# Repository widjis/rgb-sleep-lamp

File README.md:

# RGB Sleep Lamp

A USB-C-powered RGB lamp with a 3D-printed enclosure, an ESP-12F controller, and a WS2812B LED strip. This repository preserves the mechanical design, electronics revisions, custom libraries, fabrication exports, and design-review evidence.

## Mechanical design

| Assembled lamp | Transparent internal view |
| --- | --- |
|  |  |

These saved CAD previews illustrate the enclosure and internal arrangement; the component blocks in the transparent view are placement references. The latest editable enclosure is the native FreeCAD document linked below.

[Open the FreeCAD design](mechanical/freecad/RGB%20Sleep%20Lamp.FCStd) · [Assembly animation](mechanical/freecad/RGB-Sleep-Lamp-native-assembly.mp4) · [Exploded-view animation](mechanical/freecad/RGB-Sleep-Lamp-explode-reverse.mp4)

## Open the current designs

| Design | Main file |
| --- | --- |
| Editable mechanical enclosure | [RGB Sleep Lamp.FCStd](mechanical/freecad/RGB%20Sleep%20Lamp.FCStd) |
| Electronics E5 project | [circuit.kicad_pro](electronic-design/revisions/5/circuit.kicad_pro) |
| E5 PCB | [circuit.kicad_pcb](electronic-design/revisions/5/circuit.kicad_pcb) |
| E5 schematic | [circuit.kicad_sch](electronic-design/revisions/5/circuit.kicad_sch) |
| E5 fabrication package | [Gerber ZIP](electronic-design/revisions/5/fabrication/20261031-E5/RGB-Sleep-Lamp-E5-Gerber-20261031.zip) |

Open the electronics through its KiCad project so the included project settings and local footprint library are available. The E5 layout was saved and checked with KiCad 10.0.7. Custom footprints, artwork and component models are included beside the design files.

## Hardware

- ESP-12F / ESP8266 controller.
- WS2812B strip: 50 cm, 60 LEDs/metre, 30 LEDs total.
- Power architecture: USB-C PD source, PDC004 fixed-20 V trigger module, 5 V buck converter, then 3.3 V regulation for the controller.
- The LED strip operates from the 5 V rail. No mains circuitry is inside the enclosure.
- Rounded PCB outline, three mounting holes, GPIO/programming headers and LED output connector.

## E5 status

All E4 track/via routing was removed and rebuilt. E5 retains the physical component placement, pad geometry/nets, models, PCB outline and curved ORANGEFLAVOR LABS artwork. Reference labels were adjusted around the new via holes.

- Minimum track width and copper-clearance rule: **0.3 mm**.
- All 33 vias: **0.8 mm drill / 1.2 mm outside copper diameter**.
- Approximately 71.85% of routed track length is on the top layer.
- Top power/GND pours and bottom GND pour are included.
- Recorded native DRC: **0 violations, 0 unconnected items, 0 schematic-parity issues**, with all DRC checks active and no exclusions.
- Native board renders, GerbView review and fabrication ZIP checksums are recorded in [validation.json](electronic-design/revisions/5/validation.json).

These are digital validation results from 2026-10-31. Physical fit, donor-component dimensions/values, thermal, RF and functional testing remain provisional or not run. The fabrication package is marked `PRODUCTION_REVIEW_PENDING`.

[Bottom view](electronic-design/revisions/5/renders/pcb-e5-bottom.png) · [DRC report](electronic-design/revisions/5/drc-final.rpt)

## Repository layout

- `mechanical/freecad/`: native working enclosure, checkpoints, review images and assembly media.
- `mechanical/revisions/`: preserved mechanical revisions through R9 and their original source/exports. These historical exports may differ from the newer editable FreeCAD document.
- `mechanical/printing/`: existing printer-specific print outputs.
- `electronic-design/revisions/`: preserved electronics E1–E5, libraries, models, checks and exports.
- `electronic-design/planning/`: earlier placement and mechanical-planning material.
- `documentation/`: attachments, design checks, named backups and original project metadata.

Relative compatibility links such as `current-electronics`, `current-mechanical`, `electronics`, and `revisions` are preserved. `electronic-design/current` points to E5; `mechanical/current` points to the R9 export snapshot. Use the editable FreeCAD file above for ongoing enclosure work.

Named design checkpoints and explicit revision folders are versioned. OS metadata, editor locks, KiCad local UI state and editor-internal `.history` repositories stay local.

## Firmware

Application firmware and Google Home integration are planned; this initial import contains the hardware design. WLED, a custom ESP8266 firmware, and the integration approaches discussed for the lamp have not yet been installed or validated on this hardware.

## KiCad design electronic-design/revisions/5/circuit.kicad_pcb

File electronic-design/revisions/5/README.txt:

RGB SLEEP LAMP - ELECTRONICS REVISION E5

Rebuilt from E4 after removing all 444 track segments and 34 vias. All routing objects in E5 have new UUIDs. Physical footprints, pad geometry/nets, placement, 43 component models, 47 reference labels, curved artwork and board outline are retained. Five reference labels and two board labels were adjusted to keep clear of the new via bores; a short R12 leader was added.

RULES
- Clearance >=0.3 mm; every actual track width >=0.3 mm.
- Via drill 0.8 mm, outside diameter 1.2 mm, radial annular ring 0.2 mm (user clarified that 0.8 mm means the bore).
- Existing copper-edge limit 0.35 mm and other design limits retained.
- F.Cu prioritized; B.Cu used to finish connections. Existing top supply/GND and bottom GND pours refilled.

PROCESS
- Top-only trial verified 213 segments, 100% top, no vias, at widths >=0.3 mm, but incomplete.
- Complete candidate uses fanout before routing to avoid boxed-in ESP pins. All 15 undersized fanout segments generated by the router were widened to 0.3 mm and verified by native DRC.
- A clearance-checked 0.5 mm bridge at J7 pin 7 fixes a local 3.3 V thermal island; zone boundaries/settings and footprint pads are unchanged.
- Full native DRC with refill, schematic parity, all severities/checks enabled and no exclusions: 0 violations / 0 unconnected / 0 parity issues.
- E4 and its fabrication package are preserved.

EVIDENCE
validation.json; drc-final.json; routing/rebuild-baseline.json; routing/result-fanout-noopt.json; routing/fanout-width-corrections.json; routing/thermal-bridge.json.

Physical donor footprints/values, module dimensions, thermal, loop stability, RF and hardware operation remain provisional or NOT_RUN. DRC clean is a digital layout check, not fabrication approval.

FINAL REVIEW / EXPORT
Native top/bottom renders and GerbView copper/legend/profile/drill overlays inspected. Text-stroke clearance from all via bores >=0.1 mm; no collisions. 47 visible component references.
Fabrication ZIP: fabrication/20261031-E5/RGB-Sleep-Lamp-E5-Gerber-20261031.zip (10 native files; README/checksums outside ZIP). 68 PTH holes, minimum drill 0.8 mm; 3 NPTH mounting holes, 3.2 mm. ZIP and embedded file checksums verified.

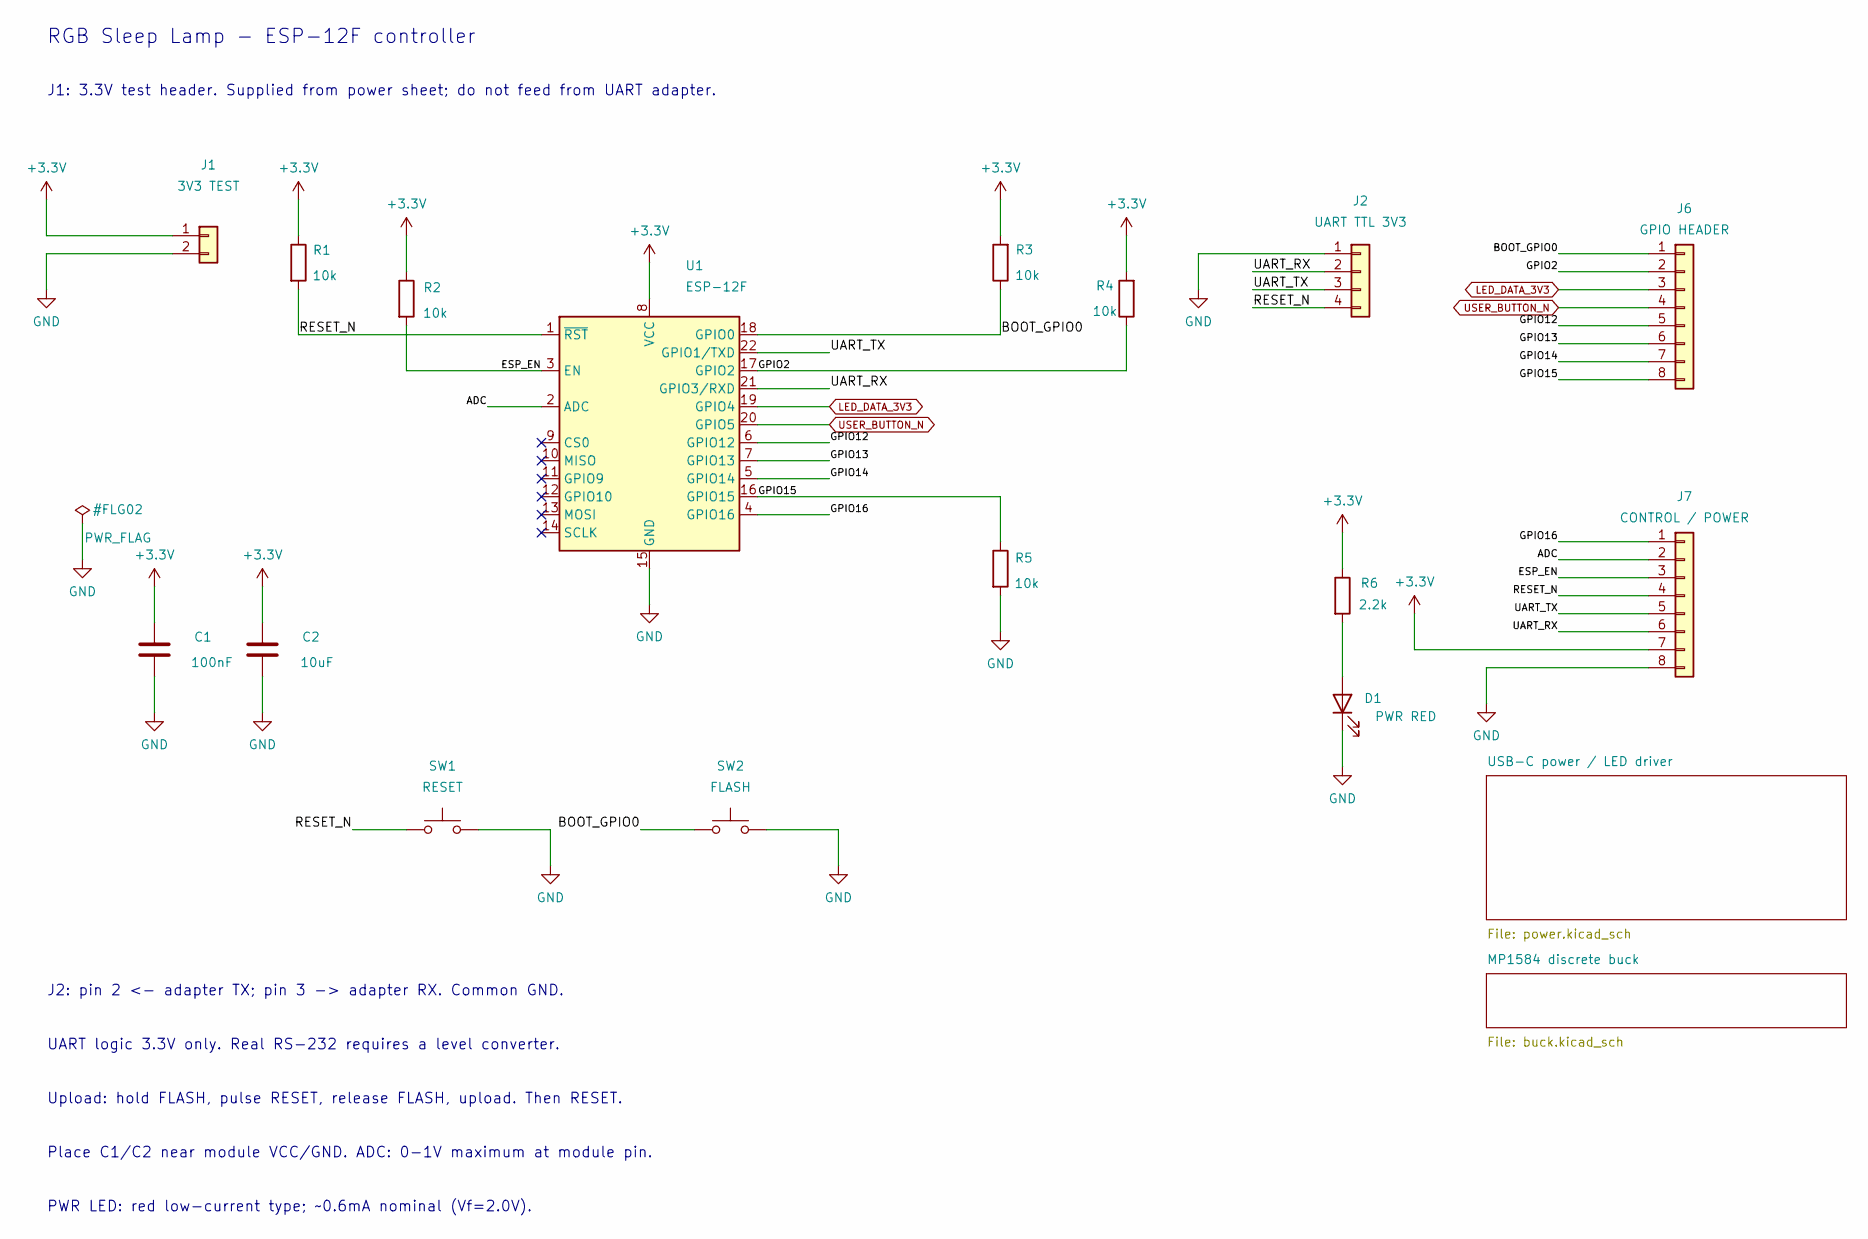
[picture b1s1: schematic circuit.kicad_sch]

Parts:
C1: 100nF; C_0805_2012Metric
C2: 10uF; C_0805_2012Metric
D1: PWR RED; LED_0805_2012Metric
J1: 3V3 TEST; PinHeader_1x02_P2.54mm_Vertical
J2: UART TTL 3V3; PinHeader_1x04_P2.54mm_Vertical
J6: GPIO HEADER; PinHeader_1x08_P2.54mm_Vertical
J7: CONTROL / POWER; PinHeader_1x08_P2.54mm_Vertical
R1, R2, R3, R4, R5: 10k; R_0805_2012Metric
R6: 2.2k; R_0805_2012Metric
SW1: RESET; SW_SPST_PTS645Sx43SMTR92
SW2: FLASH; SW_SPST_PTS645Sx43SMTR92
U1: ESP-12F; ESP-12F_AntennaOverhang

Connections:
+3.3V: C1.1, C2.1, J1.1, J7.7, R1.1, R2.1, R3.2, R4.2, R6.1, U1.8 (VCC); also elsewhere on the board
/ADC: J7.2, U1.2 (ADC)
/BOOT_GPIO0: J6.1, R3.1, SW2.1, U1.18 (GPIO0)
/ESP_EN: J7.3, R2.2, U1.3 (EN)
/GPIO2: J6.2, R4.1, U1.17 (GPIO2)
/GPIO12: J6.5, U1.6 (GPIO12)
/GPIO13: J6.6, U1.7 (GPIO13)
/GPIO14: J6.7, U1.5 (GPIO14)
/GPIO15: J6.8, R5.1, U1.16 (GPIO15)
/GPIO16: J7.1, U1.4 (GPIO16)
/RESET_N: J2.4, J7.4, R1.2, SW1.1, U1.1 (~RST)
/UART_RX: J2.2, J7.6, U1.21 (GPIO3/RXD)
/UART_TX: J2.3, J7.5, U1.22 (GPIO1/TXD)
GND: C1.2, C2.2, D1.1 (K), J1.2, J2.1, J7.8, R5.2, SW1.2, SW2.2, U1.15 (GND); also elsewhere on the board
LED_DATA_3V3: J6.3, U1.19 (GPIO4); also elsewhere on the board
unnamed: D1.2 (A), R6.2
USER_BUTTON_N: J6.4, U1.20 (GPIO5); also elsewhere on the board

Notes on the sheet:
J2: pin 2 <- adapter TX; pin 3 -> adapter RX. Common GND.
PWR LED: red low-current type; ~0.6mA nominal (Vf=2.0V).
UART logic 3.3V only. Real RS-232 requires a level converter.
Upload: hold FLASH, pulse RESET, release FLASH, upload. Then RESET.
Place C1/C2 near module VCC/GND. ADC: 0-1V maximum at module pin.
RGB Sleep Lamp - ESP-12F controller
J1: 3.3V test header. Supplied from power sheet; do not feed from UART adapter.

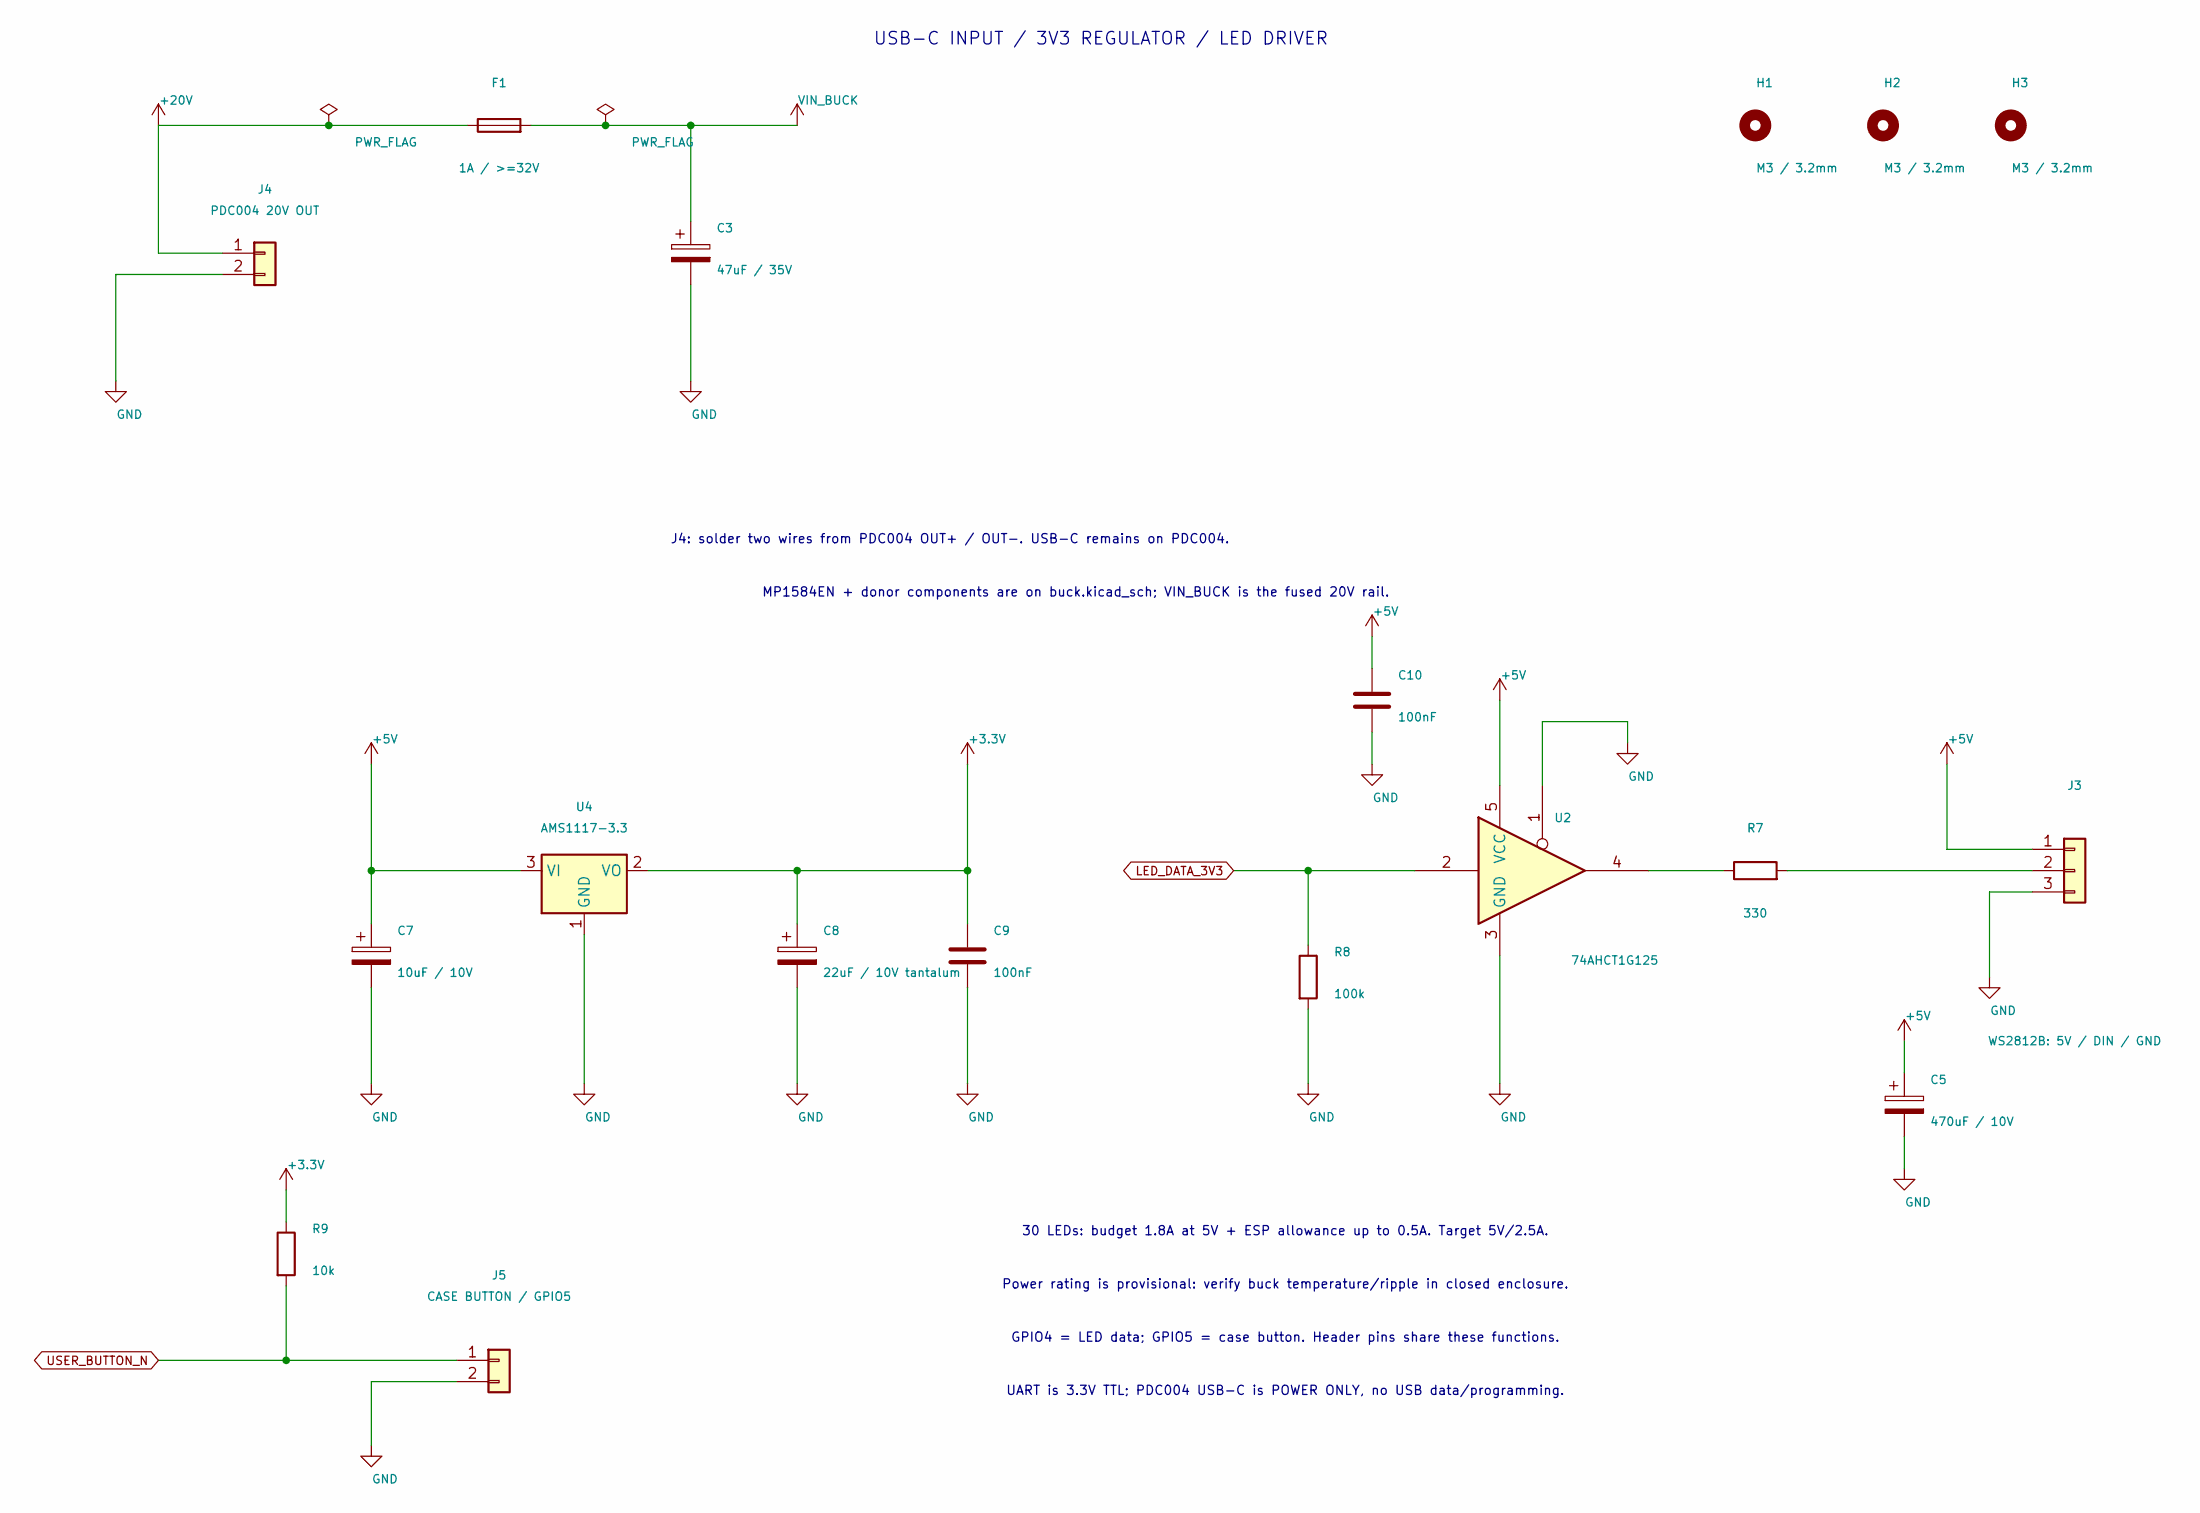
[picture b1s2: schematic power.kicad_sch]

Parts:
C3: 47uF / 35V; CP_Radial_D6.3mm_P2.50mm
C5: 470uF / 10V; CP_Radial_D8.0mm_P3.50mm
C7: 10uF / 10V; CP_Elec_5x5.4
C8: 22uF / 10V tantalum; CP_EIA-6032-28_Kemet-C
C9, C10: 100nF; C_0805_2012Metric
F1: 1A / >=32V; Fuse_1206_3216Metric
H1, H2, H3: M3 / 3.2mm; MountingHole_3.2mm_M3
J3: WS2812B: 5V / DIN / GND; LED_1x03_WirePads
J4: PDC004 20V OUT; PD20_1x02_WirePads
J5: CASE BUTTON / GPIO5; PinHeader_1x02_P2.54mm_Vertical
R7: 330; R_0805_2012Metric
R8: 100k; R_0805_2012Metric
R9: 10k; R_0805_2012Metric
U2: 74AHCT1G125; SOT-23-5
U4: AMS1117-3.3; SOT-223-3_TabPin2

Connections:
+3.3V: C8.1, C9.1, R9.1, U4.2 (VO); also elsewhere on the board
+5V: C5.1, C7.1, C10.1, J3.1, U2.5 (VCC), U4.3 (VI); also elsewhere on the board
+20V: F1.1, J4.1
GND: C3.2, C5.2, C7.2, C8.2, C9.2, C10.2, J3.3, J4.2, J5.2, R8.2, U2.1, U2.3 (GND), U4.1 (GND); also elsewhere on the board
LED_DATA_3V3: R8.1, U2.2; also elsewhere on the board
unnamed: J3.2, R7.2
unnamed: R7.1, U2.4
USER_BUTTON_N: J5.1, R9.2; also elsewhere on the board
VIN_BUCK: C3.1, F1.2; also elsewhere on the board

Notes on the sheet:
GPIO4 = LED data; GPIO5 = case button. Header pins share these functions.
MP1584EN + donor components are on buck.kicad_sch; VIN_BUCK is the fused 20V rail.
30 LEDs: budget 1.8A at 5V + ESP allowance up to 0.5A. Target 5V/2.5A.
USB-C INPUT / 3V3 REGULATOR / LED DRIVER
UART is 3.3V TTL; PDC004 USB-C is POWER ONLY, no USB data/programming.
J4: solder two wires from PDC004 OUT+ / OUT-. USB-C remains on PDC004.
Power rating is provisional: verify buck temperature/ripple in closed enclosure.

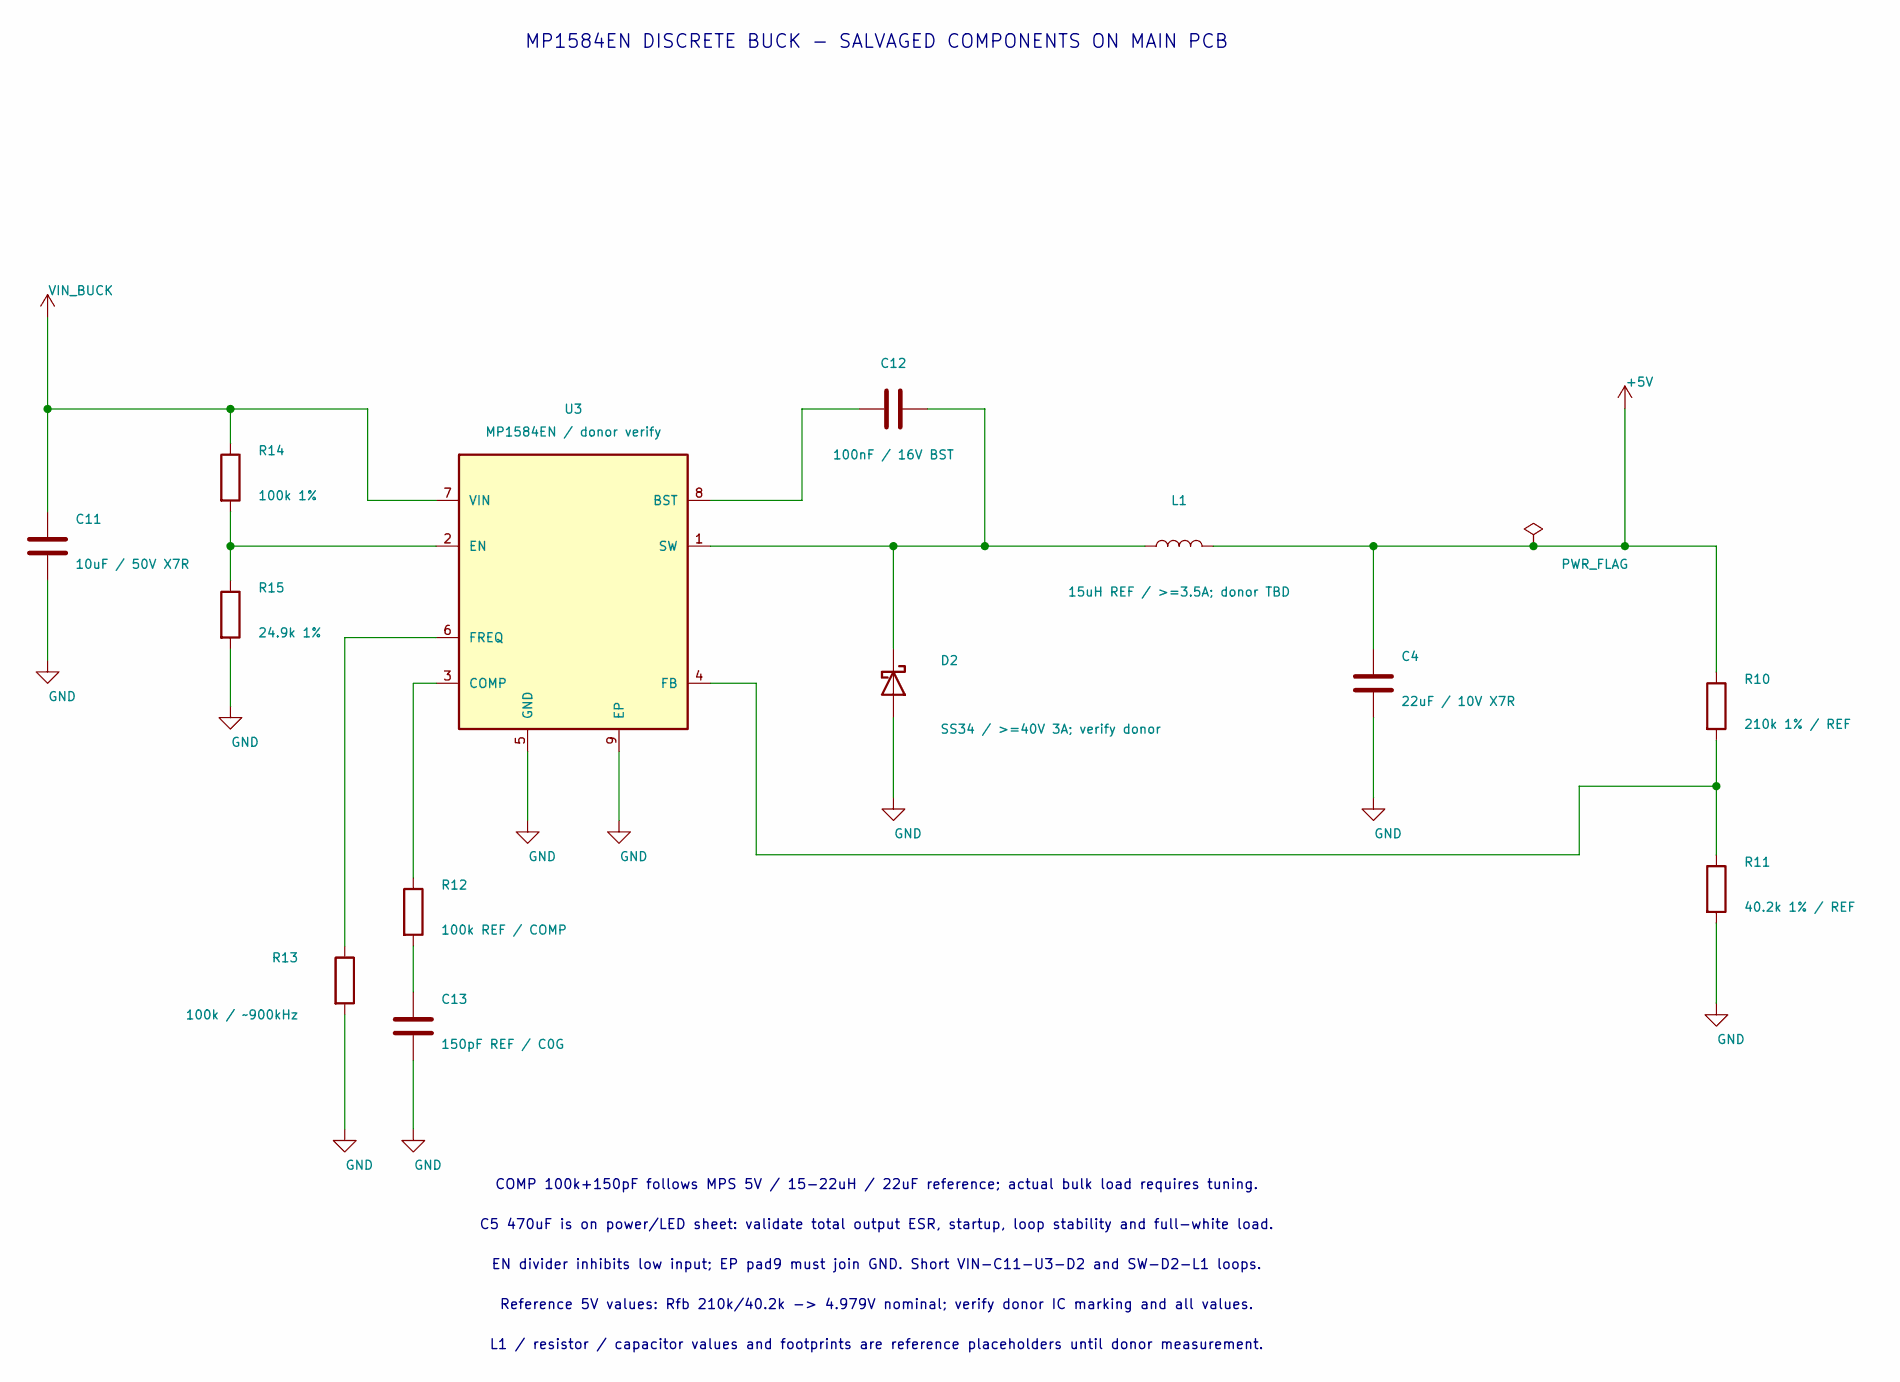
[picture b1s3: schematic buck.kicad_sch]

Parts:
C4: 22uF / 10V X7R; C_1210_3225Metric
C11: 10uF / 50V X7R; C_1210_3225Metric
C12: 100nF / 16V BST; C_0805_2012Metric
C13: 150pF REF / C0G; C_0805_2012Metric
D2: SS34 / >=40V 3A; verify donor; D_SMA
L1: 15uH REF / >=3.5A; donor TBD; L_Bourns_SRP1245A
R10: 210k 1% / REF; R_0805_2012Metric
R11: 40.2k 1% / REF; R_0805_2012Metric
R12: 100k REF / COMP; R_0805_2012Metric
R13: 100k / ~900kHz; R_0805_2012Metric
R14: 100k 1%; R_0805_2012Metric
R15: 24.9k 1%; R_0805_2012Metric
U3: MP1584EN / donor verify; MP1584EN_SOIC8E_0603CLR

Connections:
+5V: C4.1, L1.2, R10.1; also elsewhere on the board
GND: C4.2, C11.2, C13.2, D2.2 (A), R11.2, R13.2, R15.2, U3.5 (GND), U3.9 (EP); also elsewhere on the board
unnamed: C13.1, R12.2
unnamed: C12.2, D2.1 (K), L1.1, U3.1 (SW)
unnamed: C12.1, U3.8 (BST)
unnamed: R12.1, U3.3 (COMP)
unnamed: R14.2, R15.1, U3.2 (EN)
unnamed: R10.2, R11.1, U3.4 (FB)
unnamed: R13.1, U3.6 (FREQ)
VIN_BUCK: C11.1, R14.1, U3.7 (VIN); also elsewhere on the board

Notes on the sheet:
COMP 100k+150pF follows MPS 5V / 15-22uH / 22uF reference; actual bulk load requires tuning.
C5 470uF is on power/LED sheet: validate total output ESR, startup, loop stability and full-white load.
MP1584EN DISCRETE BUCK - SALVAGED COMPONENTS ON MAIN PCB
EN divider inhibits low input; EP pad9 must join GND. Short VIN-C11-U3-D2 and SW-D2-L1 loops.
Reference 5V values: Rfb 210k/40.2k -> 4.979V nominal; verify donor IC marking and all values.
L1 / resistor / capacitor values and footprints are reference placeholders until donor measurement.

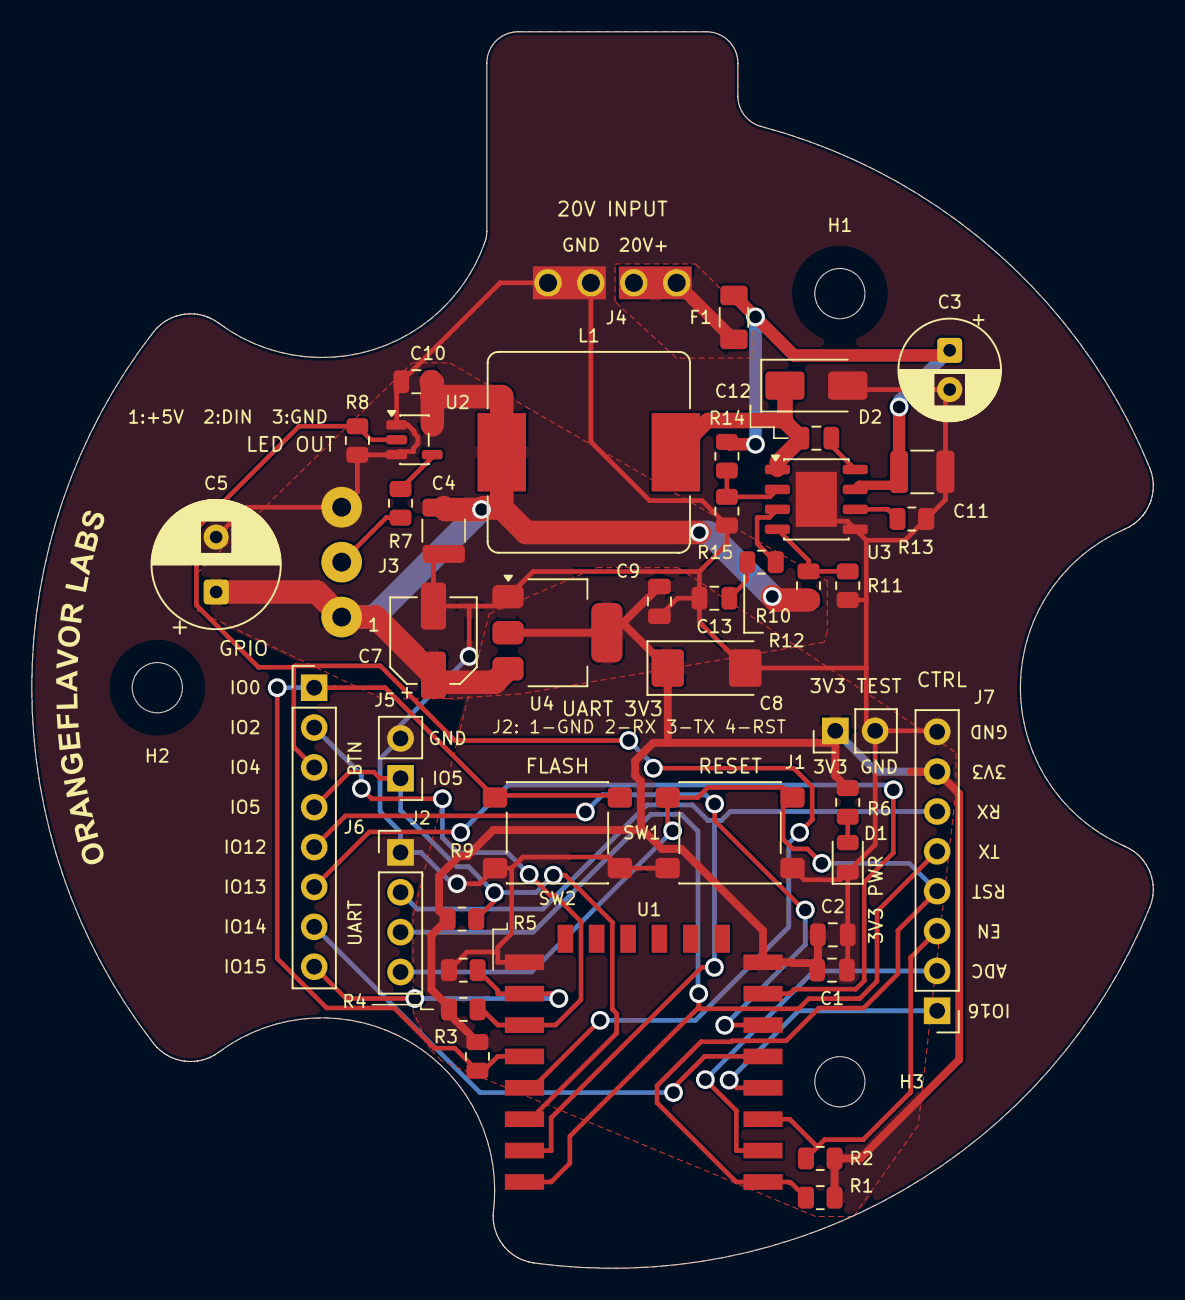
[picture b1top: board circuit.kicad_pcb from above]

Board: 2 copper layers, 71.5 x 78.8 mm, 47 parts (0 on the bottom side), 29 nets.

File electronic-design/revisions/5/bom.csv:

Reference,Value,Footprint
C1,100nF,Capacitor_SMD:C_0805_2012Metric
C2,10uF,Capacitor_SMD:C_0805_2012Metric
D1,PWR RED,LED_SMD:LED_0805_2012Metric
J1,3V3 TEST,Connector_PinHeader_2.54mm:PinHeader_1x02_P2.54mm_Vertical
J2,UART TTL 3V3,Connector_PinHeader_2.54mm:PinHeader_1x04_P2.54mm_Vertical
J6,GPIO HEADER,Connector_PinHeader_2.54mm:PinHeader_1x08_P2.54mm_Vertical
J7,CONTROL / POWER,Connector_PinHeader_2.54mm:PinHeader_1x08_P2.54mm_Vertical
R1,10k,Resistor_SMD:R_0805_2012Metric
R2,10k,Resistor_SMD:R_0805_2012Metric
R3,10k,Resistor_SMD:R_0805_2012Metric
R4,10k,Resistor_SMD:R_0805_2012Metric
R5,10k,Resistor_SMD:R_0805_2012Metric
R6,2.2k,Resistor_SMD:R_0805_2012Metric
SW1,RESET,Button_Switch_THT:SW_PUSH_6mm
SW2,FLASH,Button_Switch_THT:SW_PUSH_6mm
U1,ESP-12F,Lamp_Local:ESP-12F_AntennaOverhang
C3,47uF / 35V,Capacitor_THT:CP_Radial_D6.3mm_P2.50mm
C5,470uF / 10V,Capacitor_THT:CP_Radial_D8.0mm_P3.50mm
C7,10uF / 10V,Capacitor_SMD:CP_Elec_5x5.4
C8,22uF / 10V tantalum,Capacitor_Tantalum_SMD:CP_EIA-6032-28_Kemet-C
C9,100nF,Capacitor_SMD:C_0805_2012Metric
C10,100nF,Capacitor_SMD:C_0805_2012Metric
F1,1A / >=32V,Fuse:Fuse_1206_3216Metric
H1,M3 / 3.2mm,MountingHole:MountingHole_3.2mm_M3
H2,M3 / 3.2mm,MountingHole:MountingHole_3.2mm_M3
H3,M3 / 3.2mm,MountingHole:MountingHole_3.2mm_M3
J3,WS2812B: 5V / DIN / GND,Connector_Lamp:LED_1x03_WirePads
J4,PDC004 20V OUT,Connector_Lamp:PD20_1x02_WirePads
J5,CASE BUTTON / GPIO5,Connector_PinHeader_2.54mm:PinHeader_1x02_P2.54mm_Vertical
R7,330,Resistor_SMD:R_0805_2012Metric
R8,100k,Resistor_SMD:R_0805_2012Metric
R9,10k,Resistor_SMD:R_0805_2012Metric
U2,74AHCT1G125,Package_TO_SOT_SMD:SOT-23-5
U4,AMS1117-3.3,Package_TO_SOT_SMD:SOT-223-3_TabPin2
C4,22uF / 10V X7R,Capacitor_SMD:C_1210_3225Metric
C11,10uF / 50V X7R,Capacitor_SMD:C_1210_3225Metric
C12,100nF / 16V BST,Capacitor_SMD:C_0805_2012Metric
C13,150pF REF / C0G,Capacitor_SMD:C_0805_2012Metric
D2,SS34 / >=40V 3A; verify donor,Diode_SMD:D_SMA
L1,15uH REF / >=3.5A; donor TBD,Inductor_SMD:L_Bourns_SRP1245A
R10,210k 1% / REF,Resistor_SMD:R_0805_2012Metric
R11,40.2k 1% / REF,Resistor_SMD:R_0805_2012Metric
R12,100k REF / COMP,Resistor_SMD:R_0805_2012Metric
R13,100k / ~900kHz,Resistor_SMD:R_0805_2012Metric
R14,100k 1%,Resistor_SMD:R_0805_2012Metric
R15,24.9k 1%,Resistor_SMD:R_0805_2012Metric
U3,MP1584EN / donor verify,Lamp_Local:MP1584EN_SOIC8E_0603CLR
